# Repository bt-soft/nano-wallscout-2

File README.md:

# Wallscout – impulzus-indukciós (PI) betonvas-kereső firmware

ATmega328P (16 MHz), DD tekercs-elrendezés, SSD1306 128x64 OLED, 2 gomb, passzív buzzer.
Build: PlatformIO (`pio run`), az U8g2 könyvtárat a `platformio.ini` húzza be.

## 1. Hardver (a kapcsolási rajz alapján)

| Funkció | Láb | Megjegyzés |
|---|---|---|
| TX MOSFET (Q2, IRLZ44N) kapu | PD2 | aktív magas, 100 Ω soros + 10 kΩ lehúzó |
| Buzzer (Q1 2N2222 bázis) | PD3 = OC2B | Timer2 Fast PWM |
| SW2 „Nullázás” | PD4 (PCINT20) | aktív alacsony, belső felhúzás |
| SW1 „Kalibrálás” | PD5 (PCINT21) | aktív alacsony, belső felhúzás |
| Vevőjel (Rx) | PC0 = A0 | az MCP6004 U2A/U2B (2 × ~11×, össz. ~121×) + U2D kimenete, nyugalmi szint Vmid = Vcc/2 |
| Tápfeszültség | PC1 = A1 | R11 100k / R12 33k osztó → Vin = Vadc · 133/33 |
| OLED SDA / SCL | PC4 / PC5 | hardveres I2C, 400 kHz |
| Soros napló | PD0 / PD1 | a rajzon nincs kivezetve, USB-soros átalakítót kell rá kötni (115200 baud) |

A kijelző a kódban 128x64-es (`U8G2_SSD1306_128X64_NONAME_1_HW_I2C`). A rajzon szereplő ER-OLEDM0.91 128x32-es; ha ilyet használsz, a konstruktort kell cserélni a `ui.cpp`-ben.

## 2. A mérés elve és megvalósítása (`measure.cpp`)

PI fémkeresőnél a TX tekercsbe rövid áramimpulzust adunk, majd lekapcsoljuk. A tekercs lecsengésekor a közeli fémben örvényáram indul, ami lassítja a vevőjel lecsengését. Ezt a lecsengést két, a lekapcsolás után késleltetett időpontban mintavételezzük:

```
TX:  ____|‾‾‾‾‾‾‾|__________________________
         0      tp   tp+tS1   tp+tS2     period
                      S1       S2

```

* **S1** – korai minta (`tS1`, alapérték és minimum 40 µs): a tekercsáram lecsengése után vett minta; a minimumot úgy választottuk, hogy 12 V-on, 60 µs impulzusnál (számított lecsengés ≈ 28 µs, lásd lentebb) se essen a lecsengésbe.
* **S2** – késői minta (`tS2`, alapérték 60 µs): csak a lassan lecsengő (nagyobb, vasas) válaszok maradnak benne.
* A fém jelenléte az S1 (és S2) nullázott értékének eltolódásaként látszik.

**Időzítés:** egy impulzus alatt a megszakítások tiltottak (`cli()`), az időt a Timer1 adja (előosztó 1, 1 tick = 62,5 ns). A Timer1 a TX bekapcsolásakor nullázódik, a kódban aktív várakozás (`while (TCNT1 < …)`) biztosítja az időpontokat, így nincs megszakítás-jitter.

**ADC:** közvetlen regiszterprogramozás, előosztó 16 → 1 MHz ADC órajel, konverzió 13 µs. Az ADC a konverzió indítása után 1,5 ADC órajellel mintavételez, ezért a konverziót ennyivel (`ADC_SAMPLE_TICKS` = 24 tick) korábban indítjuk, hogy a valódi mintavétel pontosan `tS1`, illetve `tS2` időnél legyen. Az S2 konverzió csak az S1 befejezése után indul, ezért `tS2 ≥ tS1 + 16 µs` (a Beállítások kikényszeríti). A névleges 200 kHz feletti ADC órajel pontosságát az átlagolás ellensúlyozza.

**Átlagolás:** egy ciklus 32 impulzus átlaga (500 Hz-nél ~64 ms); a nullázás normál ciklusokat futtat, amíg a jel meg nem áll (lásd 5. fejezet). Az impulzusokat 8-as csomagokban futtatjuk, a csomagok között a gombokat pollozzuk (a megszakítások az impulzusok közti várakozás alatt engedélyezettek, hogy a `millis()` pontos maradjon).

### 2.1. Az időzítési paraméterek jelentése, számítása és korlátai

**Mitől értendők az értékek?**

| Paraméter | Mettől számít | Jelentés |
|---|---|---|
| Impulzus (`tp`) | a TX bekapcsolásától (a Timer1 nullázásától) | a TX bekapcsolva tartásának ideje |
| S1 késleltetés (`tS1`) | a **TX lekapcsolásától** | a korai mintavétel időpontja |
| S2 késleltetés (`tS2`) | a **TX lekapcsolásától** | a késői mintavétel időpontja |
| Frekvencia (`f`) | – | az impulzusok ismétlési frekvenciája, a periódus `T = 1/f` |

Az S1 és az S2 késleltetés **ugyanabból a pillanatból**, a TX lekapcsolásától indul, nem egymás után: `tS2 = 60 µs` azt jelenti, hogy a lekapcsolás után 60 µs-mal történik a mintavétel, nem az S1 után 60 µs-mal. A Timer1 a TX bekapcsolásától számol, ezért a mintavételek a Timer1 szerint `tp + tS1`, illetve `tp + tS2` időnél vannak.

**Újraszámítás tick-ekre** (`measureConfigure()`, 16 MHz-en 1 µs = 16 tick; a Beállítások módosítása után minden alkalommal lefut):

```
g_tpTicks     = tp · 16
g_t1Ticks     = tp · 16 + tS1 · 16 − ADC_SAMPLE_TICKS     (az S1 konverzió indítási ideje)
g_t2Ticks     = tp · 16 + tS2 · 16 − ADC_SAMPLE_TICKS     (az S2 konverzió indítási ideje)
g_periodTicks = 16 000 000 / f                            (a periódus hossza)
```

Az `ADC_SAMPLE_TICKS` (24 tick = 1,5 µs) az ADC konverzió-indítása és a tényleges mintavétel közti késés, ezért a konverziót ennyivel korábban indítjuk. A legnagyobb érték (`tp + tS2` = 150 + 800 µs = 15 200 tick) belefér a Timer1 16 bitjébe (max. 65 535 tick = 4,1 ms).

**Egy periódus időrendje:**

```
t = 0                  TX BE, Timer1 = 0
t = tp                 TX KI
t = tp + tS1 − 1,5 µs   S1 konverzió indul  → kész: ~tp + tS1 + 11,5 µs
t = tp + tS2 − 1,5 µs   S2 konverzió indul  → kész: ~tp + tS2 + 11,5 µs
t = T                  a következő impulzus (a hátralévő időt várakozás tölti ki)
```

**Korlátok (amiket a Beállítások kikényszerít, `settingsSanitize()`):**

1. **Tartományok:** impulzus 20…150 µs, S1 40…120 µs, S2 60…800 µs, frekvencia 250…2500 Hz.
2. **S2 az S1 után:** a két konverzió nem fedheti egymást, mert az ADC egy időben csak egy konverziót végez, ezért `tS2 ≥ tS1 + 16 µs` (13 µs konverzió + 3 µs tartalék, `MIN_S_GAP_US`). Ha S1 növelése ezt megsértené, az S2 automatikusan feljebb ugrik.
3. **Bele kell férnie a periódusba:** a teljes mérésnek (impulzus + S2 késleltetés + az S2 konverzió ideje + tartalék) a `T` periódus alá kell esnie. Különben a következő impulzus csak a mérés végén indulhat, és a tényleges frekvencia a beállítottnál kisebb lenne (a mérés ráadásul csendben elcsúszna). Ezért a frekvencia felső határa:

   ```
   f_max = min(2500, 1 000 000 / (tp + tS2 + 13 + 10))   [Hz; a µs-értékekkel]
   ```

   (13 µs az ADC konverzió, 10 µs a `PERIOD_MARGIN_US` tartalék.) Példák: 60 µs impulzus + 60 µs S2 → `f_max` = 2500 Hz; 60 µs + 400 µs → ~2100 Hz; 150 µs + 800 µs → ~1000 Hz; 60 µs + 800 µs → ~1130 Hz.
4. **A frekvencia alsó határa 250 Hz:** 16 MHz-en a 16 bites Timer1 periódus-számlálója `16 000 000 / 250` = 64 000 tick-ig (4 ms) fér be (a maximum 65 535).
5. **Az S1 minimuma (40 µs) a tekercsáram lecsengéséből adódik.** Egyszerű modell (L = 1 mH, tp = 60 µs, a tekercs és a MOSFET ellenállását elhanyagolva, tehát felső becslés): a csúcsáram `I ≈ U·tp/L` = 0,54 A (9 V) … 0,72 A (12 V), a lecsípés (≈ 38 V) miatti lecsengési idő `t ≈ U·tp/(U_lecsípés − U)` ≈ 19 µs (9 V) … 28 µs (12 V). A 40 µs ezt ~1,4× tartalékkal fedi. Hosszabb impulzusnál vagy alacsonyabb lecsípésnél a lecsengés tovább tart (arányos tp-vel), ilyenkor az S1-et növelni kell. A szám számított, nem mért érték: szkóppal ellenőrizendő (Rx jel a „TX folyamatos" móddal).

**Mi történik módosításkor?**

A fenti korlátokat a `settingsSanitize()` ([src/settings.cpp](src/settings.cpp)) kényszeríti ki. Ez lefut minden beállításmódosítás után (`settingsAdjust()`), betöltéskor (`settingsLoad()`) és mentéskor (`settingsSave()`). A frekvencia felső határát a `freqLimitHz()` számolja. A korrekció csendben történik, a kijelzőn nincs jelzés.

* Az impulzus vagy az S2 növelése csökkentheti a frekvencia felső határát; ha a beállított frekvencia a határ fölé kerülne, a firmware automatikusan a határra csökkenti.
* Az S1 növelése szükség esetén az S2-t is feljebb viszi (`tS2 ≥ tS1 + 16`), ami szintén csökkentheti a frekvencia felső határát.
* A frekvencia léptetése a mindenkori felső határnál ugrik vissza a minimumra (250 Hz).
* Minden módosítás után a mérés új időzítéssel (`measureConfigure()`) folytatódik, és a Beállítások elhagyásakor új nullázás következik, mert a nyugalmi jelszint a paraméterekkel együtt változik.
* A mérési ciklus ideje (32 impulzus) a frekvenciával fordítottan változik (500 Hz: ~64 ms, 2500 Hz: ~13 ms); a tényleges soros naplózási és kijelzési ütem a kijelző rajzolási idejétől függ, ezért ~5–6 Hz marad.
* A **TX folyamatos** menüpont (lásd 4. fejezet) ugyanezekkel a `tp` és `f` értékekkel fut, és a módosításuk azonnal érvényesül.

### 2.2. A felpörgetett ADC és a beállítható időértékek összeegyeztethetősége

Az ATmega328P ADC-je a datasheet szerint 50…200 kHz ADC órajelen ad teljes (10 bites) felbontást. A firmware az előosztót 16-ra állítja (`ADC_PRESCALER`), így az ADC órajele 16 MHz / 16 = **1 MHz**, vagyis a névleges tartomány fölött jár. Ennek oka, hogy a konverzió (13 órajel = 13 µs) így elég gyors ahhoz, hogy a lecsengés korai szakaszában két mintát vegyünk. A beállítható időértékek és az ADC együttműködése:

* **A konverzió időzítése pozitív marad.** A konverzió indítása és a tényleges mintavétel közt 1,5 ADC órajel (1,5 µs, 24 CPU ciklus) telik el, ezért az indítást `ADC_SAMPLE_TICKS`-szel korábbra tesszük. A legkisebb beállítható késleltetés `tS1 = 40 µs`, így az indítási időpont `tp + 40 − 1,5 = tp + 38,5 µs`, azaz mindig az impulzus lekapcsolása után van (a TX kikapcsolása előtt soha nem indul konverzió).
* **A két konverzió nem fedi egymást.** Az ADC egy időben egyetlen konverziót végez (13 µs). Az S2 konverzió indítása `tS2 − 1,5 µs`, az S1 befejezése `tS1 − 1,5 + 13 µs`, ezért kell `tS2 ≥ tS1 + 16 µs` (13 µs konverzió + 3 µs tartalék). A `settingsSanitize()` ezt minden módosításnál kikényszeríti, szükség esetén az S2-t feljebb viszi.
* **A hosszú késleltetések nem okoznak gondot.** Az S2 800 µs-ig állítható. Az ADC a konverzió indításáig nem fut, a mintavétel pillanatát kizárólag a Timer1-es várakozás határozza meg, ezért a hosszú várakozás nem befolyásolja az ADC működését vagy pontosságát. A korlát nem az ADC, hanem a periódus (lásd 2.1).
* **Az indítási bizonytalanság kicsi.** Az ADC előosztója szabadon fut, ezért a konverzió valójában a következő ADC órajel-élnél indul: ez legfeljebb 1 ADC órajelnyi (1 µs, 16 CPU ciklus) bizonytalanság a mintavétel idejében. A lassan lecsengő jelnél ez elhanyagolható, a legkorábbi (40 µs körüli) mintáknál, ahol a lecsengés meredek, kismértékű szórást okozhat. Ezt az impulzusonkénti mintavétel azonos fázisa (a Timer1 mindig nullázott) és a 32 impulzusos átlagolás csökkenti.
* **A felbontásromlást az átlagolás ellensúlyozza.** 200 kHz fölött az ADC effektív felbontása csökken (a datasheet szerint ~1 MHz-nél kb. 8 bit körüli), a kisebb jelek zajosabbak lehetnek. A 32 impulzus átlagolása (~√32 ≈ 5,7× zajcsökkenés) ezt kompenzálja. A nullázott (`s1`, `s2`) érték így is csak néhány ADC egység nagyságú jelet tud megbízhatóan kimutatni, ezért vannak a detektálási küszöbök (`DETECT_ON_COUNTS` / `DETECT_OFF_COUNTS`).
* **Forrásimpedancia.** A mintavevő kondenzátor feltöltésére 1,5 ADC órajel jut (1,5 µs). Az Rx jelet az U2B erősítő kimenete adja (alacsony kimeneti impedancia), ezért ez rendszerint nem korlátoz. Ha a legkorábbi minta (kis `tS1`) szórása szokatlanul nagy, ez is gyanúsítható.
* **Ha gond van az ADC-vel.** Ha a kis jelek túl zajosak vagy a korai minta szór, az előosztó 32-re emelhető (`ADC_PRESCALER 32`, `ADC_PS_BITS` = `_BV(ADPS2) | _BV(ADPS0)`). Ekkor 0,5 MHz az ADC órajele, a konverzió 26 µs, a mintavétel 3 µs-mal az indítás után van, és az S1–S2 minimális távolság is nagyobb lesz (~29 µs). Az `ADC_SAMPLE_TICKS`, `ADC_CONV_US` és a `MIN_S_GAP_US` a `config.h`-ban az `ADC_PRESCALER`-ből számolódik, de a frekvenciahatár (2.1) és az itt említett értékek ilyenkor újra ellenőrzendők.

**Telítés:** ha az impulzusok több mint negyedénél az ADC érték ≤ 4 vagy ≥ 1019, a Keresés képernyőn „TELITES!” jelenik meg (a trimmerekkel kell finomítani).

## 3. Jelfeldolgozás (`main.cpp`)

* `base1`, `base2`: a nullázáskor mért S1, S2 átlag.
* `s1 = S1 − base1`, `s2 = S2 − base2`: **előjeles jel** (ADC egység; 1 egység ≈ 40 µV a bemeneten a ~121× erősítés mellett).
* A keresési mód naplójában `dd = S1 − S2` (nyers, nem nullázott); a DD-képernyő ettől külön, impulzus alatti mérést használ.
* **Jelerősség:** `s1` (a kijelzőn előjelesen, a sávon abszolút értékben).
* **Csúcs-megtartás és lecsengés:** a legnagyobb |s1| 0,5, másodpercig (`PEAK_HOLD_MS`) változatlanul látszik a sávon függőleges jelzőként, utána exponenciálisan lecseng az aktuális jelszint felé (időállandó 1 s, `PEAK_DECAY_MS`). Új, nagyobb csúcsnál a jelző azonnal felugrik. Így a jelző mozgásából követhető, merre és mennyit változik a jel.
* **Találat (hiszterézissel):** a találat akkor kapcsol be, ha |s1| ≥ 4 egység (`DETECT_ON_COUNTS`), és csak akkor kapcsol ki, ha 2,5 egység alá csökken (`DETECT_OFF_COUNTS`). A két küszöb közti sávban az állapot változatlan marad, így a zajszint körüli jel nem billegteti a találatot, a mélységbecslést, a fém-jelleget és a hangot. A találat-állapot nullázáskor törlődik. **Kijelzett érték:** a KERESES nagy száma és sávja (valamint a GRAFIKON fejléc száma) találat nélkül 0-t mutat, találatnál a valós előjeles értéket (`UiData::shown`); így nyugalomban a zaj nem billegteti a számot. A soros napló és a grafikon görbéje továbbra is a nyers értéket használja, a csúcsjelző is a nyers amplitúdót követi.
* **Fém-jelleg (heurisztika):** az `s1` előjele dönt. Az [include/config.h](include/config.h) fájlban a `FERROUS_S1_NEGATIVE` alapértéke `true`: `s1 < 0` → „Fe (vas)”, `s1 > 0` → „nFe (szines)”. `false` esetén a besorolás fordított. A módosításhoz újra kell fordítani és feltölteni a firmware-t; a mért jel előjele nem változik. Az `s2/s1` arány korábbi méréseknél ugrált, ezért a besorolás nem ezen alapul. A korábbi hardverbeállítással a fogó (vas) +44…+80, a bronz −26…−38 egységet adott; az előjel szerinti besorolást az aktuális beállításokkal ismert fémtárgyakon ellenőrizni kell. Az átmeneti lecsengés a kijelzett fém-jelleget is megváltoztathatja.
* **Mélységbecslés:** `d = d_ref · (A_ref / |s1|)^(1/3)`. A kitevő (3) a `DEPTH_EXPONENT` konstans. Kalibráció nélkül az alapértelmezett `A_ref = 60` egységet használja a 30 mm-hez, ezt `~35mm?` jelzi (a „?” = kalibrálatlan). Kalibráció után `35mm` jelenik meg. Zajszint alatt „--mm”, 150 mm felett „>150mm”.
* **Aktivitás:** gombnyomás, vagy a jel (DD képernyőn a `dd`) több mint 8 egységnyi változása.

## 4. Kezelés

| | Kereső csoport | Beállító csoport |
|---|---|---|
| Képernyők | **KERESES** ↔ **GRAFIKON** | **DD BEALLITAS** ↔ **BEALLITASOK** |
| SW1 rövid | váltás a két képernyő között | váltás a két képernyő között |
| SW2 rövid | újranullázás | Beállításokban: következő elem (DD-n nincs funkció) |
| SW1 hosszú | mélység-kalibráció | Beállításokban: a kijelölt elem értékének léptetése (nyomva tartva ismétlődik, a végén a minimumra ugrik) |
| SW2 hosszú | belépés a beállító csoportba (DD BEALLITAS) | **kilépés**: mentés, új időzítés alkalmazása, nullázás, KERESES |

Minden képernyő jobb felső sarkában a tápfeszültség látszik; 7,0 V alatt villogva, inverzen.

### Képernyők

A szövegek a kisebb, 95 nyomtatható ASCII-karaktert tartalmazó U8g2 `_tr` fontokat használják; a kijelző feliratai ezért ékezet nélküliek.

* **KERESES:** előjeles jelérték nagy számmal (csak a negatív érték kap „−” jelet, a „+” helye üresen marad, így a szám nem ugrál; a 0 mindig előjel nélkül jelenik meg), becsült mélység, fém-jelleg, jelerősség-sáv csúcs-jelzővel, alul állapotsor: bal oldalt `Nincs jel` vagy `TELITES!`, jobb oldalt mindig a `Skala: N` felirat (jobbra igazítva, így a sor nem ugrál).
* **GRAFIKON:** a jelerősség az idő függvényében (128 minta, kb. 20 s). A felső sorban a cím után a mód jelzése (`ABS` / `SIG`), jobbra igazítva a legfrissebb mért érték, a jobb szélen a tápfeszültség. Két mód van (Beállítások → *Grafikon*, alapértelmezés: `ABS`):
  * **ABS** – a jel abszolút értékét mutatja (a felső szám is előjel nélküli). A nullvonal a kijelző legalsó során (63. pixel) van, a teljes skála 49 pixel (a 14. sorig), így a teljes grafikon-magasság használható; a felső határt ritkán pöttyözött vonal jelzi.
  * **SIG** – előjeles megjelenítés: a nullvonal a 38. pixelen, a ±teljes skála ±24 pixel, mindkét határt ritkán pöttyözött vonal jelzi.

  A skála az érzékenységi fokozatból adódik. A mód vagy az érzékenység váltásakor az előzmények törlődnek, mert más pixel-skálán készültek.
* **DD BEALLITAS:** a DD-képernyő saját mérésében az A0 szintjét minden TX-impulzus előtt, majd az impulzus felénél vagy 3/4-énél mintavételezzük, váltakozó impulzusokon. A két időpontban külön átlagoljuk az impulzus alatti és az előtti szinteket; a nagyobb abszolút különbség kerül a kijelzőre, előjelesen, kijelzési simítás után, ADC-egységben. Az alsó sorban az ehhez tartozó két nyers átlag `B` (előtte) és `P` (impulzus alatt) látszik. Egy ciklus összesen 32 impulzusból áll. A korábbi S1 − S2 különbség hamis nullát adhatott, ha mindkét késői minta idejére visszaállt a jel. A normál keresés továbbra is az S1/S2 mintákat használja.

  A `NULL OK` akkor kapcsol be, ha a nyers és a simított különbség is legfeljebb 6 ADC-egység, és akkor kapcsol ki, ha bármelyik 7 fölé kerül. Ha bármelyik DD-minta az ADC tartományának szélére kerül, `TELITES!` látható `NULL OK` helyett. A sáv előjeles, skálája automatikus (±50 … ±1000); a szélesebb minimális skála a nullpont körül kevésbé érzékeny kijelzést ad, de a mért számot nem változtatja meg. A hang a nyers eltéréssel emelkedik, telítéskor maximális hangmagasságú. A nulla a két kiválasztott mintavételi ponton jelenti a közvetlen jel minimumát, nem garantálja a teljes jelalak minimumát vagy azt, hogy egy korábbi erősítőfokozat nem telítődött. A beállítást fémmentes környezetben, a valós készüléken, lehetőleg szkóppal is ellenőrizd. Az A0-n lévő kondenzátor, az impulzushossz és az erősítő viselkedése befolyásolja az eredményt; a mintavételi helyek és a küszöb mérés alapján hangolhatók az `include/config.h` fájlban.
* **BEALLITASOK:** elemek:
  1. *Impulzus* (20…150 µs, 10 µs-es lépés, alap 60)
  2. *Frekvencia* (250…2500 Hz, 50 Hz-es lépés, alap 500; a felső határ automatikusan csökken, ha az impulzus + S2 késleltetés + ADC konverzió (13 µs) + 10 µs tartalék nem fér bele a periódusba, pl. 60 µs impulzus és 800 µs S2 mellett kb. 1130 Hz. Ha az impulzus vagy S2 növelése miatt a beállított frekvencia a határ fölé kerülne, az a határra csökken)
  3. *S1 keslelt.* (40…120 µs, 5 µs-es lépés, alap 40; a TX lekapcsolásától számítva)
  4. *S2 keslelt.* (60…800 µs, alap 60; a TX lekapcsolásától számítva, tehát S1-gyel egy időpontból indul; legalább S1 + 16; a lépés 100 µs alatt 5, 300 µs alatt 10, fölötte 20 µs)
  5. *Erzekenyseg* (1…6 kijelzési skála; nem módosítja az analóg erősítést, a TX impulzushosszt vagy az ismétlési frekvenciát)
  6. *Hang* (KI, 1…3; a kitöltési tényezővel szabályozott hangerő)
  7. *Kal. melyseg* (10…100 mm referencia-mélység, 5 mm-es lépés; módosítása érvényteleníti a kalibrációt)
  8. *Grafikon* (SW1 hosszan: váltás `ABS` ↔ `SIG` között; alapértelmezés `ABS`)
  9. *TX folyamatos* (SW1 hosszan: `KI` ↔ `BE`, mint a többi elemnél; a TX tekercs csillapításának szkópos beállításához. `BE` állapotban a beállított impulzushosszal és frekvenciával szakadatlanul, csomagolás és mintavétel nélkül megy az impulzussor, így a szkóp stabilan ráhangolható. Közben lehet más menüelemre lépni (SW2), és az *Impulzus* és *Frekvencia* elemet állítani (SW1 hosszan): a változás azonnal hat az impulzusokra, az impulzussor csak a kijelző újrarajzolásakor szakad meg rövid időre. Az állapot nem tárolódik: a Beállításokból való kilépéskor (vagy alváskor) leáll, és visszaáll a csomagonkénti működés. Közben a készülék nem alszik el magától, ezért a teszt után kapcsold ki vagy lépj ki.)
  10. *Reset* (SW1 hosszan: visszaállítás; a „GYARI ERTEKEK” üzenet rövid ideig látszik, utána mentés, nullázás és visszatérés a KERESES képernyőre)

A beállítások a beállító csoportból való kilépéskor (vagy alvás előtt) az EEPROM-ba kerülnek (CRC védelemmel).

#### Kijelzési érzékenység / skála

| Fokozat | Teljes skála (ADC-egység) | Megjelenítés |
|---|---:|---|
| 1/6 | 500 | Legkevésbé érzékeny; azonos jel kisebb sávkitérést és kisebb grafikon-kilengést okoz. |
| 2/6 | 250 |  |
| 3/6 | 120 | Alapértelmezett fokozat. |
| 4/6 | 60 |  |
| 5/6 | 30 |  |
| 6/6 | 15 | Legérzékenyebb; azonos jel nagyobb sávkitérést és nagyobb grafikon-kilengést okoz. |

Az alacsonyabb kijelzési érzékenység **kevésbé rángatózóvá teheti a sávot, a grafikont és a hangmagasságot**, mert ugyanaz a jel kisebb kitéréssé skálázódik. Magát a nyers mérést és annak zaját nem csökkenti. A Keresés nagy, előjeles számértéke, a mélységbecslés és a fémjelzés sem változik a fokozattal; ezekhez valódi jelszűrésre vagy eltérő feldolgozásra lenne szükség. Ez tehát kijelzési skála, nem a hardver érzékenységét vagy az impulzusprofilt módosító üzemmód.

### Mélység-kalibráció

1. A Beállításokban állítsd be a referencia-mélységet (pl. 30 mm).
2. Tartsd az eszközt ismert, ennyire lévő vas fölé (a nullázás után, fémmentes helyen).
3. A KERESES vagy GRAFIKON képernyőn nyomd hosszan az SW1-et. Az aktuális |s1| lesz a referencia-amplitúdó, az EEPROM-ba mentődik.

#### Betanítás a gyakorlatban

A mélység-kijelzés betanításához először állítsd be annak a próbadarabnak a távolságát, amelyet használni fogsz, majd nullázás után tartsd a műszert a megfelelő mélységben lévő vas fölé. Ha a jel stabil, a KERESES vagy GRAFIKON képernyőn az SW1 hosszú megnyomása eltárolja az aktuális jelerősséget ehhez a távolsághoz. Ezután a készülék ezt a mért referenciajelet használja a mélység becsléséhez; a betanított érték kikapcsolás után is megmarad. A kalibráció a becslést hangolja, nem helyettesíti a fémmentes helyen végzett nullázást.

### Hang

A jelerősséggel arányos hangmagasság (500…3000 Hz) a Timer2 Fast PWM kimenetén (OC2B, PD3). A hang a találat-állapot fennállása alatt szólal meg (hiszterézissel: 4 egység fölött kezdődik, 2,5 alatt áll le). A hangerőt a kitöltési tényező (6 % / 20 % / 50 %) adja.

## 5. Nullázás, alvás, ébredés

* **Bekapcsoláskor** a logó után automatikusan nullázás (adaptív nullázás, lásd lent), majd a KERESES képernyő.
* **Nullázás közben** (fémmentes helyen tartsd a tekercset!) először röviden megjelenik a „NULLAZAS...” keretes felirat, majd a bázismérés alatt a normál KERESES vagy GRAFIKON képernyő frissül, a felirat nélkül. Erre azért van szükség, mert a kijelző képe és tápterhelése befolyásolhatja a vevő referenciáját; a felirat alatti bázismérés után a grafikonon tartós eltolódást figyeltünk meg. A nullázás normál mérési ciklusokat futtat (32 impulzus, közben kijelző-frissítés), és addig tart, amíg a jel meg nem áll: a legutóbbi `ZERO_WINDOW` (6) ciklus S1 értékeinek max−min különbsége `ZERO_STABLE_COUNTS` (1,6 egység) alá kerül. A nullpont ennek az ablaknak az átlaga. Ha a jel nem áll meg, `ZERO_MAX_CYCLES` (40, kb. 7 s) után a legutóbbi ablakot használja. A stabilitásra várás a gombnyomás utáni átmeneti ingadozást is kivárja. A nullázás kb. 1,5–7 s. A KERESES↔GRAFIKON váltáskor (SW1) automatikus nullázás van, amely az újonnan megjelenő képernyő rajzolása mellett fut (a grafikon előzménye is törlődik), így váltást fémmentes helyen végezz. A jelzés nélküli bázismérés hatását a valós készüléken ellenőrizni kell.
* **5 perc aktivitás nélkül** (nincs gomb, nincs jelváltozás) a készülék elmenti az esetleges beállításokat, kikapcsolja a kijelzőt és a hangot, az ADC-t, a BOD-ot, majd Power-down alvásba lép.
* **Ébredés:** bármelyik gomb (PD4/PD5 pin-change megszakítás). Az ébresztő nyomás nem vált ki műveletet; a készülék azonnal nulláz és a KERESES képernyőre lép.
* A megszakítás csak az alváshoz kell: mérés közben a megszakítások tiltottak, ébredés után a PCINT ki van kapcsolva, a gombokat pollozzuk.

## 6. Soros napló (115200 baud)

Indulás után fejléc és CSV sorok mérési ciklusonként (kb. 5–6 Hz):

```
# ms,scr,S1raw,S2raw,base1,base2,s1,s2,dd,peak,depth_mm,vbatt_mV,sat
```

| Mező | Jelentés |
|---|---|
| `scr` | keresési CSV képernyője: 0 KERESES, 1 GRAFIKON |
| `S1raw`, `S2raw` | nyers ADC átlag (0..1023, nyugalmi ~512) |
| `base1`, `base2` | nullázáskor eltárolt alapszint |
| `s1` | `S1raw − base1` (előjeles jel; a kijelzett jelerősség) |
| `s2` | `(S1raw − S2raw) − (base1 − base2)`, az S1 − S2 különbség nullázott megfelelője |
| `dd` | `S1raw − S2raw` a keresési mód mérésében; nem a DD-képernyő jele |
| `peak` | csúcs-megtartott abszolút érték |
| `depth_mm` | becsült mélység; −1 nincs találat, −2 túl mély |
| `vbatt_mV` | tápfeszültség |
| `sat` | 1, ha az ADC telítésben van |

Eseménysorok `#`-tel kezdődnek: `# ZERO`, `# CAL`, `# SET …`, `# SLEEP`, `# WAKE`. A DD-képernyőn CSV helyett `# DD baseline=… pulse=… dd=… sat=…` sor jelenik meg a kiválasztott mintapár simítatlan átlagával. A hangoláshoz érdemes a fém fölé húzva figyelni az `s1` előjelét és az `s1`/`S2raw` viszonyát (fém-jelleg küszöb), a `sat` jelzőt és az `S1raw`/`S2raw` nyugalmi értékeit (a trimmerek beállításához).

## 7. Forrásfájlok

| Fájl | Tartalom |
|---|---|
| `include/*.h` | konstansok (`config.h`: lábkiosztás, időzítések, küszöbök) és a modulok fejlécei |
| `src/main.cpp` | állapotgép, jelfeldolgozás, mélységbecslés, napló |
| `src/measure.cpp` | PI mérés, ADC, Timer1, tápfeszültség-mérés |
| `src/settings.cpp` | beállítások, EEPROM |
| `src/buzzer.cpp` | Timer2 hangkeltés |
| `src/buttons.cpp` | gombkezelés |
| `src/power.cpp` | mélyalvás, ébresztés |
| `src/ui.cpp` | OLED képernyők |

## 8. Ismert korlátok, hangolási teendők

* A mélységbecslés és a fém-jelleg közelítő modell; az `DEPTH_EXPONENT` és az alapértelmezett `CAL_AMP_DEF` a valós hardveren, a soros napló alapján hangolandó. A fém-jelleg csak az `s1` előjelén alapul; a megfordított besorolást az aktuális hardverbeállítással több ismert fémmel is ellenőrizni kell.
* A tápfeszültség-kijelzés pontossága a 7805 kimenetétől (ADC referencia) függ; szükség esetén a `VREF_MV` / `VBATT_OFFSET_MV` állítható. Ha a mért érték a bemeneti dióda miatt eltér a tápegységétől, az utóbbival korrigálható.
* A flash kihasználtsága ~90 %, új funkcióknál ezt figyelni kell.
* A mérés közben szóló buzzer (a meghajtás áramfelvétele) befolyásolhatja a vevőt, ami a hang ki-be kapcsolásakor billegő jelet adhat. Ha ez zavaró, csökkentsd a hangerőt vagy kapcsold ki a hangot (Beállítások → *Hang*).
* A feliratok ékezet nélküliek (a kijelző-betűkészlet nem tartalmaz ő/ű karaktert).

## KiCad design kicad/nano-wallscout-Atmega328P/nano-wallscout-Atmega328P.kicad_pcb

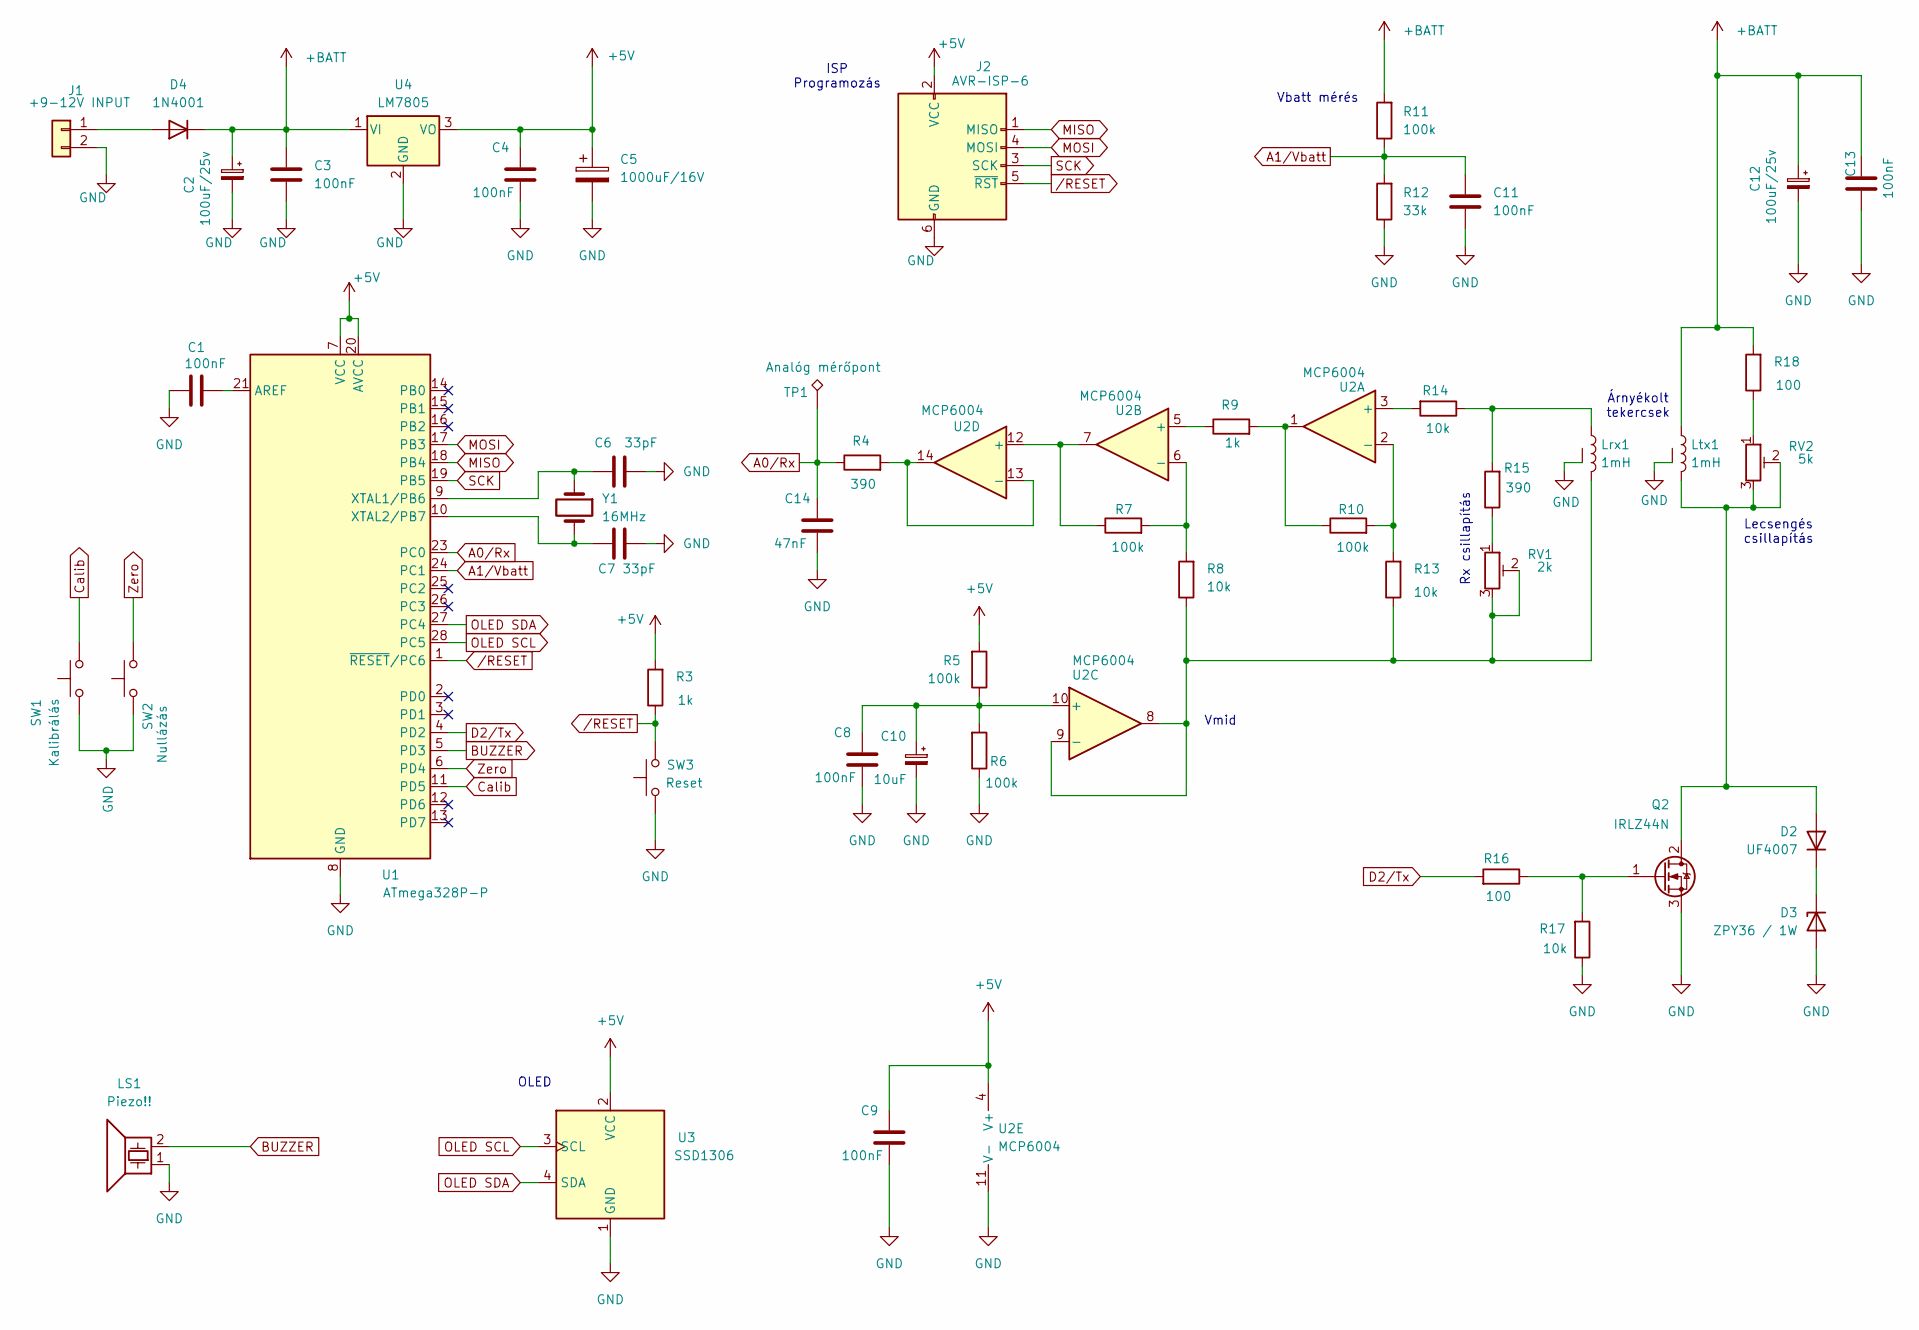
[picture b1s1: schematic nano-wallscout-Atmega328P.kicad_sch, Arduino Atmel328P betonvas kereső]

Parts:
C1, C3, C4, C8, C9, C11, C13: 100nF; C_Rect_L7.2mm_W2.5mm_P5.00mm
C2, C12: 100uF/25v; CP_Radial_D6.3mm_P2.50mm
C5: 1000uF/16V; CP_Radial_D10.0mm_P5.00mm
C6, C7: 33pF; C_Disc_D3.0mm_W2.0mm_P2.50mm
C10: 10uF; CP_Radial_D6.3mm_P2.50mm
C14: 47nF; C_Rect_L7.2mm_W2.5mm_P5.00mm
D2: UF4007; D_DO-35_SOD27_P10.16mm_Horizontal
D3: ZPY36 / 1W; D_DO-35_SOD27_P10.16mm_Horizontal
D4: 1N4001; D_DO-41_SOD81_P10.16mm_Horizontal
J1: +9-12V INPUT; TerminalBlock_Phoenix_PT-1,5-2-5.0-H_1x02_P5.00mm_Horizontal
J2: AVR-ISP-6; PinHeader_2x03_P2.54mm_Vertical
LS1: Piezo!!; PinHeader_2x01_P2.54mm_Vertical
Lrx1: 1mH; TerminalBlock_Phoenix_PT-1,5-3-3.5-H_1x03_P3.50mm_Horizontal
Ltx1: 1mH; TerminalBlock_Phoenix_PT-1,5-3-3.5-H_1x03_P3.50mm_Horizontal
Q2: IRLZ44N; TO-220-3_Vertical
R3, R9: 1k; R_Axial_DIN0207_L6.3mm_D2.5mm_P10.16mm_Horizontal
R4, R15: 390; R_Axial_DIN0207_L6.3mm_D2.5mm_P10.16mm_Horizontal
R5, R6, R7, R10, R11: 100k; R_Axial_DIN0207_L6.3mm_D2.5mm_P10.16mm_Horizontal
R8, R13, R14, R17: 10k; R_Axial_DIN0207_L6.3mm_D2.5mm_P10.16mm_Horizontal
R12: 33k; R_Axial_DIN0207_L6.3mm_D2.5mm_P10.16mm_Horizontal
R16, R18: 100; R_Axial_DIN0207_L6.3mm_D2.5mm_P10.16mm_Horizontal
RV1: 2k; Potentiometer_Bourns_3266Y_Vertical
RV2: 5k; Potentiometer_Bourns_3266Y_Vertical
SW1: Kalibrálás; SW_PUSH_6mm_H8mm
SW2: Nullázás; SW_PUSH_6mm_H8mm
SW3: Reset; SW_PUSH_6mm_H8mm
TP1: Analóg mérőpont; TestPoint_Loop_D2.50mm_Drill1.0mm
U1: ATmega328P-P; DIP-28_W7.62mm
U2: MCP6004; DIP-14_W7.62mm_LongPads
U3: SSD1306; PinHeader_1x04_P2.54mm_Vertical
U4: LM7805; TO-220-3_Vertical
Y1: 16MHz; Crystal_HC49-4H_Vertical

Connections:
+5V: C4.2, C5.1, C9.2, J2.2 (VCC), R3.2, R5.2, U1.7 (VCC), U1.20 (AVCC), U2.4 (V+), U3.2 (VCC), U4.3 (VO)
+BATT: C2.1, C3.1, C12.1, C13.2, D4.1 (K), Ltx1.1, R11.2, R18.2, U4.1 (VI)
A0/Rx: C14.2, R4.1, TP1.1 (1_1), U1.23 (PC0)
A1/Vbatt: C11.1, R11.1, R12.2, U1.24 (PC1)
BUZZER: LS1.2, U1.5 (PD3)
Calib: SW1.2, U1.11 (PD5)
D2/Tx: R16.2, U1.4 (PD2)
GND: C1.2, C2.2, C3.2, C4.1, C5.2, C6.1, C7.1, C8.1, C9.1, C10.2, C11.2, C12.2, C13.1, C14.1, D3.2 (A), J1.2, J2.6 (GND), LS1.1, Lrx1.3 (SHIELD), Ltx1.3 (SHIELD), Q2.3 (S), R6.1, R12.1, R17.1, SW1.1, SW2.1, SW3.1, U1.8 (GND), U1.22 (GND), U2.11 (V-), U3.1 (GND), U4.2 (GND)
MISO: J2.1 (MISO), U1.18 (PB4)
MOSI: J2.4 (MOSI), U1.17 (PB3)
unnamed: D2.2 (A), Ltx1.2, Q2.2 (D), RV2.2, RV2.3
unnamed: D2.1 (K), D3.1 (K)
unnamed: D4.2 (A), J1.1
unnamed: Lrx1.1, R14.1, R15.2
unnamed: Q2.1 (G), R16.1, R17.2
unnamed: R9.2, R10.1, U2.1
unnamed: R15.1, RV1.1
unnamed: R18.1, RV2.1
unnamed: C1.1, U1.21 (AREF)
unnamed: C6.2, U1.9 (XTAL1/PB6), Y1.1
unnamed: C7.2, U1.10 (XTAL2/PB7), Y1.2
unnamed: R14.2, U2.3 (+)
unnamed: R10.2, R13.2, U2.2 (-)
unnamed: R9.1, U2.5 (+)
unnamed: R7.2, R8.2, U2.6 (-)
unnamed: C8.2, C10.1, R5.1, R6.2, U2.10 (+)
unnamed: Lrx1.2, R8.1, R13.1, RV1.2, RV1.3, U2.8, U2.9 (-)
unnamed: R7.1, U2.7, U2.12 (+)
unnamed: R4.2, U2.13 (-), U2.14
OLED SCL: U1.28 (PC5), U3.3 (SCL)
OLED SDA: U1.27 (PC4), U3.4 (SDA)
SCK: J2.3 (SCK), U1.19 (PB5)
Zero: SW2.2, U1.6 (PD4)
/RESET: J2.5 (~RST), R3.1, SW3.2, U1.1 (~RESET/PC6)

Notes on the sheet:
Lecsengés csillapítás
Vmid
Árnyékolt tekercsek
Rx csillapítás
Vbatt mérés
ISP Programozás
OLED

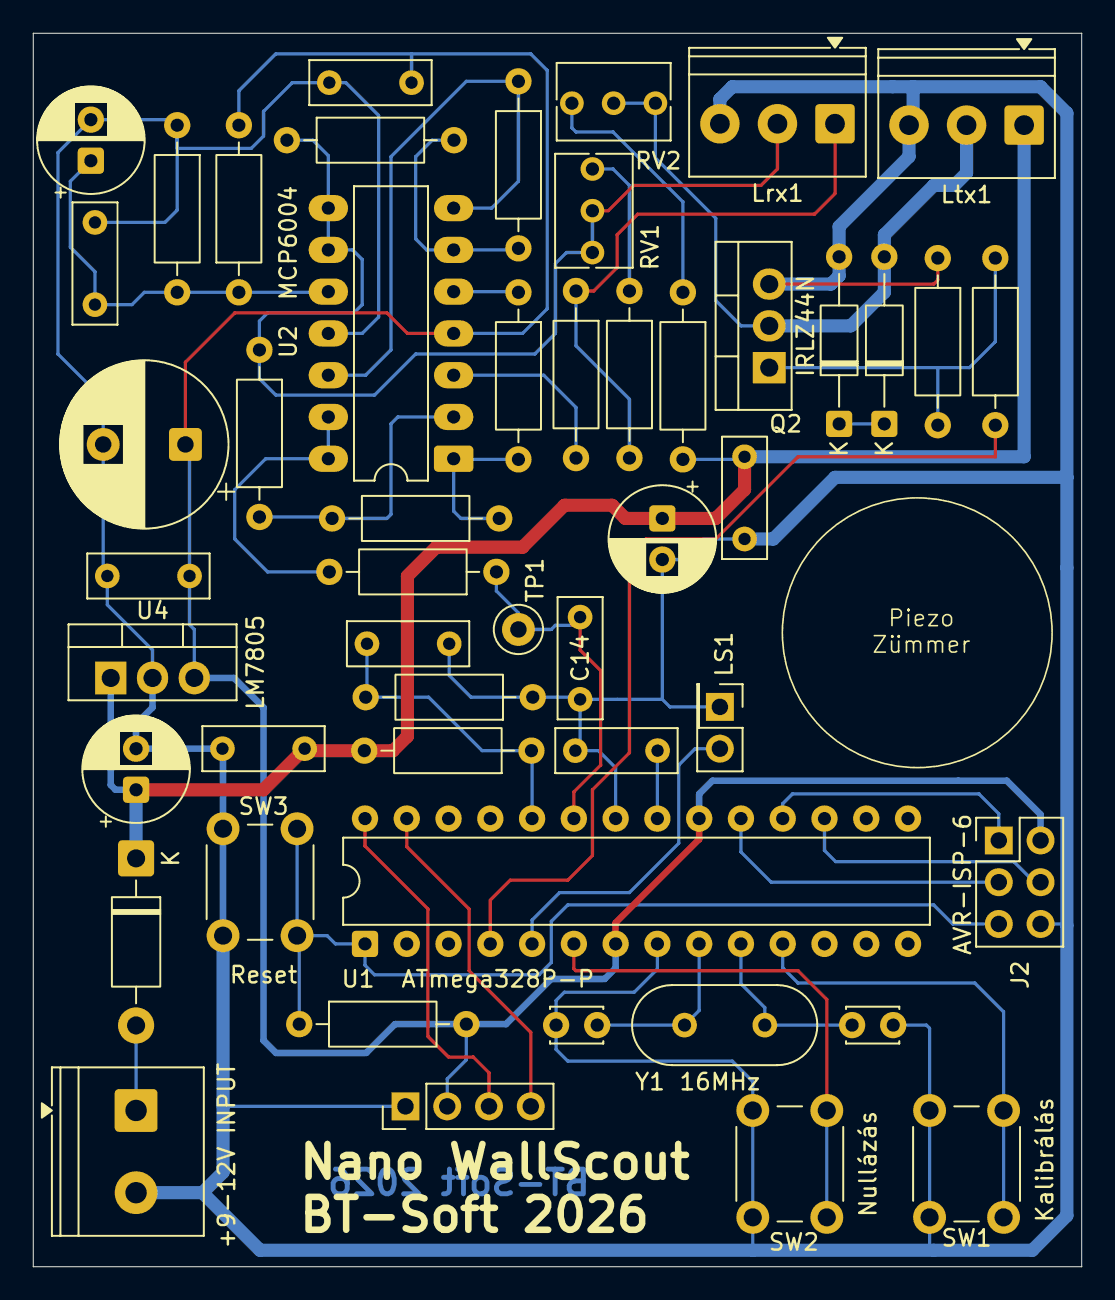
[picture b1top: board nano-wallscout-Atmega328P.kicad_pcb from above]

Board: 2 copper layers, 63.8 x 75.0 mm, 50 parts (0 on the bottom side), 34 nets.

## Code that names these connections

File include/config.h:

/**
 * @file config.h
 * @brief A firmware központi konfigurációja: lábkiosztás, időzítések, küszöbök.
 *
 * Itt található minden hardverhez kötött és hangolható konstans, hogy a többi
 * modulban ne legyenek "mágikus számok".
 */
#pragma once
#include <Arduino.h>

/* ------------------------------------------------------------------ */
/* Általános                                                          */
/* ------------------------------------------------------------------ */

/** Soros napló engedélyezése */
// #define LOG_ENABLED

/** Soros port sebessége (baud). */
#define LOG_BAUD 115200

/* ------------------------------------------------------------------ */
/* Lábkiosztás (a kapcsolási rajz alapján)                            */
/* ------------------------------------------------------------------ */

/** Adó (TX) MOSFET kapuja: PD2 (D2/Tx). Aktív magas (R16 = 100R sorosan, R17 = 10k lehúzó). */
#define TX_PORT PORTD // TX kimenet portja
#define TX_DDR DDRD   // TX kimenet irányítása
#define TX_BIT PD2    // TX kimenet bitje

/** Passzív buzzer meghajtó tranzisztor (Q1) bázisa: PD3 = OC2B (Timer2 PWM kimenet). */
#define BUZZER_DDR DDRD   // Buzzer kimenet irányítása
#define BUZZER_PORT PORTD // Buzzer kimenet portja
#define BUZZER_BIT PD3    // Buzzer kimenet bitje

/** Gombok (aktív alacsony, belső felhúzással): SW1 "Kalibrálás" = PD5, SW2 "Nullázás" = PD4. */
#define BTN_PIN PIND    // Gombok bemeneti portja
#define BTN_PORT PORTD  // Gombok kimeneti portja (felhúzás)
#define BTN_DDR DDRD    // Gombok irányítása
#define BTN_SW1_BIT PD5 // SW1 bitje
#define BTN_SW2_BIT PD4 // SW2 bitje

/** ADC csatornák: A0 = vevőjel (Rx, a Vmid = Vcc/2 körül), A1 = tápfeszültség osztó. */
#define ADC_CH_RX 0    // ADC csatorna a vevőjelhez (A0)
#define ADC_CH_VBATT 1 // ADC csatorna a tápfeszültség osztóhoz (A1)

/* ------------------------------------------------------------------ */
/* ADC és időzítés                                                    */
/* ------------------------------------------------------------------ */

/**
 * ADC előosztó. 16 -> 1 MHz ADC órajel, egy konverzió 13 us.
 * (A névleges 50..200 kHz-nél gyorsabb, a pontosság kicsit romlik, ezt az átlagolás ellensúlyozza.)
 * Érvényes értékek: 2, 4, 8, 16, 32, 64, 128. A hozzá tartozó ADPS biteket az ADC_PS_BITS adja.
 */
#define ADC_PRESCALER 16       // ADC előosztó
#define ADC_PS_BITS _BV(ADPS2) // ADPS bitek az előosztóhoz

/** Timer1 tick-ek száma 1 us alatt (Timer1 előosztó = 1, így 1 tick = 1 CPU ciklus = 62,5 ns). */
#define TICKS_PER_US (F_CPU / 1000000UL)
/** A konverzió indítása és a tényleges mintavétel (S&H) közti idő: 1,5 ADC órajel (CPU ciklusban). */
#define ADC_SAMPLE_TICKS ((3 * ADC_PRESCALER) / 2)
/** Egy ADC konverzió ideje us-ban (13 ADC órajel). */
#define ADC_CONV_US ((13 * ADC_PRESCALER) / 16)
/** Az S1 és S2 minta közti minimális távolság (us): konverzióidő + biztonsági tartalék. */
#define MIN_S_GAP_US (ADC_CONV_US + 3)

/** Egy mérési ciklusban átlagolt impulzusok száma. */
#define PULSES_PER_CYCLE 32
/** Nullázáskor a stabilitás-vizsgálat ablaka (ciklusok száma); a nullpont ennek az átlaga. */
#define ZERO_WINDOW 6
/** Az ablakban az S1 értékek max-min különbsége ennél kisebb (ADC egység) → a jel megállt. */
#define ZERO_STABLE_COUNTS 1.6f
/** A nullázás legfeljebb ennyi mérési ciklusig tart (ha a jel nem áll meg). */
#define ZERO_MAX_CYCLES 40
/** Egyszerre lefuttatott impulzusok száma (két csomag között a gombokat is pollozzuk). */
#define PULSE_CHUNK 8

/** ADC telítés-detektálás: ennél kisebb / nagyobb nyers érték telítésnek számít. */
#define ADC_SAT_LOW 4
#define ADC_SAT_HIGH 1019

/* ------------------------------------------------------------------ */
/* Állítható paraméterek határai és alapértékei                       */
/* ------------------------------------------------------------------ */

#define PULSE_MIN_US 20  // Minimális impulzusidő us-ban
#define PULSE_MAX_US 150 // Maximális impulzusidő us-ban
#define PULSE_DEF_US 60  // Alapértelmezett impulzusidő us-ban

#define FREQ_MIN_HZ 250  // Minimális frekvencia Hz-ben
#define FREQ_MAX_HZ 2500 // Maximális frekvencia Hz-ben
#define FREQ_DEF_HZ 500  // Alapértelmezett frekvencia Hz-ben

#define S1_MIN_US 40  // Minimális S1 késleltetés us-ban (a tekercsáram lecsengése után; lásd README 2.1)
#define S1_MAX_US 120 // Maximális S1 késleltetés us-ban
#define S1_DEF_US 40  // Alapértelmezett S1 késleltetés us-ban

#define S2_MIN_US 60  // Minimális S2 késleltetés us-ban (legalább S1_MIN_US + MIN_S_GAP_US)
#define S2_MAX_US 800 // Maximális S2 késleltetés us-ban
#define S2_DEF_US 60  // Alapértelmezett S2 késleltetés us-ban

/** Biztonsági tartalék (us) a periódus végén: a frekvencia felső határa az impulzus + S2 + konverzió + ennyi alapján adódik. */
#define PERIOD_MARGIN_US 10

/** Az érzékenység-fokozatok száma (a fullscale értékek a settings.cpp-ben). */
#define SENS_COUNT 6   // Az érzékenység-fokozatok száma
#define SENS_DEF_IDX 2 // Alapértelmezett érzékenység-fokozat indexe

#define CAL_DEPTH_MIN_MM 10  // Minimális kalibrációs mélység mm-ben
#define CAL_DEPTH_MAX_MM 100 // Maximális kalibrációs mélység mm-ben
#define CAL_DEPTH_DEF_MM 30  // Alapértelmezett kalibrációs mélység mm-ben
#define CAL_AMP_DEF 60.0f    // Kalibráció nélküli alapértelmezett referencia-amplitúdó (ADC egység) a CAL_DEPTH_DEF_MM mélységhez

/* ------------------------------------------------------------------ */
/* Jelfeldolgozás                                                     */
/* ------------------------------------------------------------------ */

/** Ennél kisebb |jel| (ADC egység, nullázás után) zajnak számít; a kalibráció minimális jelszintjének alapja. */
#define DETECT_MIN_COUNTS 3.0f
/** Találat bekapcsolási küszöbe (ADC egység). */
#define DETECT_ON_COUNTS 4.0f
/** Találat kikapcsolási küszöbe (ADC egység); a két küszöb közti sáv a hiszterézis, ami megakadályozza a billegést. */
#define DETECT_OFF_COUNTS 2.5f
/** A vas jelének előjele: true = negatív S1, false = pozitív S1; az ellenkező előjel színesfém. */
#define FERROUS_S1_NEGATIVE true
/** A mélységbecslés modelljének kitevője: amplitúdó ~ 1/mélység^n. */
#define DEPTH_EXPONENT 3.0f
/** A becsült mélység felső határa (mm); efölött ">max" jelenik meg. */
#define DEPTH_MAX_MM 150
/** A csúcs-megtartás ideje (ms), utána a csúcs exponenciálisan lecseng az aktuális érték felé. */
#define PEAK_HOLD_MS 500UL
/** A csúcs lecsengésének időállandója (ms): ennyi idő alatt csökken a különbség ~63 %-ára. */
#define PEAK_DECAY_MS 1000UL
/** DD képernyőn ennyi eltérés (ADC egység) alatt "OK" a nullpont. */
#define DD_OK_COUNTS 6.0f
/** DD minták helye a TX impulzuson belül: 2/4 és 3/4, külön impulzusokon. */
#define DD_SAMPLE_EARLY_NUM 2
#define DD_SAMPLE_LATE_NUM 3
#define DD_SAMPLE_DEN 4

/* ------------------------------------------------------------------ */
/* Tápfeszültség mérés                                                */
/* ------------------------------------------------------------------ */

/** Az osztó: R11 = 100k (felső), R12 = 33k (alsó) -> Vin = Vadc * 133 / 33. */
#define VBATT_DIV_NUM 133UL
#define VBATT_DIV_DEN 33UL
/** Az ADC referencia (AVcc, a 7805 kimenete) mV-ban. Pontosítható multiméteres méréssel. */
#define VREF_MV 5000UL
/** Utólagos korrekció mV-ban (pl. a bemeneti dióda esése, ha a kijelzett érték eltér). */
#define VBATT_OFFSET_MV 0
/** Ennél kisebb tápfeszültségnél (mV) alacsony elem figyelmeztetés. */
#define VBATT_LOW_MV 7000
/** A tápfeszültség mérésének periódusa (ms). */
#define VBATT_PERIOD_MS 500UL

/* ------------------------------------------------------------------ */
/* Gombok és alvás                                                    */
/* ------------------------------------------------------------------ */

#define BTN_DEBOUNCE_MS 25UL
/** Ennyi ideig tartó nyomás hosszú nyomásnak számít. */
#define BTN_LONG_MS 700UL
/** Hosszú nyomás alatt ennyi ms-onként ismétlődik az esemény. (ennyi időnként változik a menüben a menüelem értéke) */
#define BTN_REPEAT_MS 500UL

/** Inaktivitás ideje (ms) mélyalvásig: 5 perc. */
#define SLEEP_TIMEOUT_MS 300000UL
/** Ekkora jelváltozás (ADC egység) aktivitásnak számít. */
#define ACTIVITY_DELTA 8.0f

/** A grafikon előzményeinek hossza (pixel / minta). */
#define HIST_LEN 128
/** A grafikon függőleges kitérése a nullvonaltól (pixel): a teljes skála ennyi pixelnek felel meg. */
#define GRAPH_HALF_RANGE_PX 24
/** Abszolút értékes (ABS) módban a nullvonal ezen a soron van (a kijelző legalsó sora). */
#define GRAPH_ABS_ZERO_Y 63
/** ABS módban a teljes skála ennyi pixelnek felel meg (a felső sor alatti 14. sorig). */
#define GRAPH_ABS_RANGE_PX 49
